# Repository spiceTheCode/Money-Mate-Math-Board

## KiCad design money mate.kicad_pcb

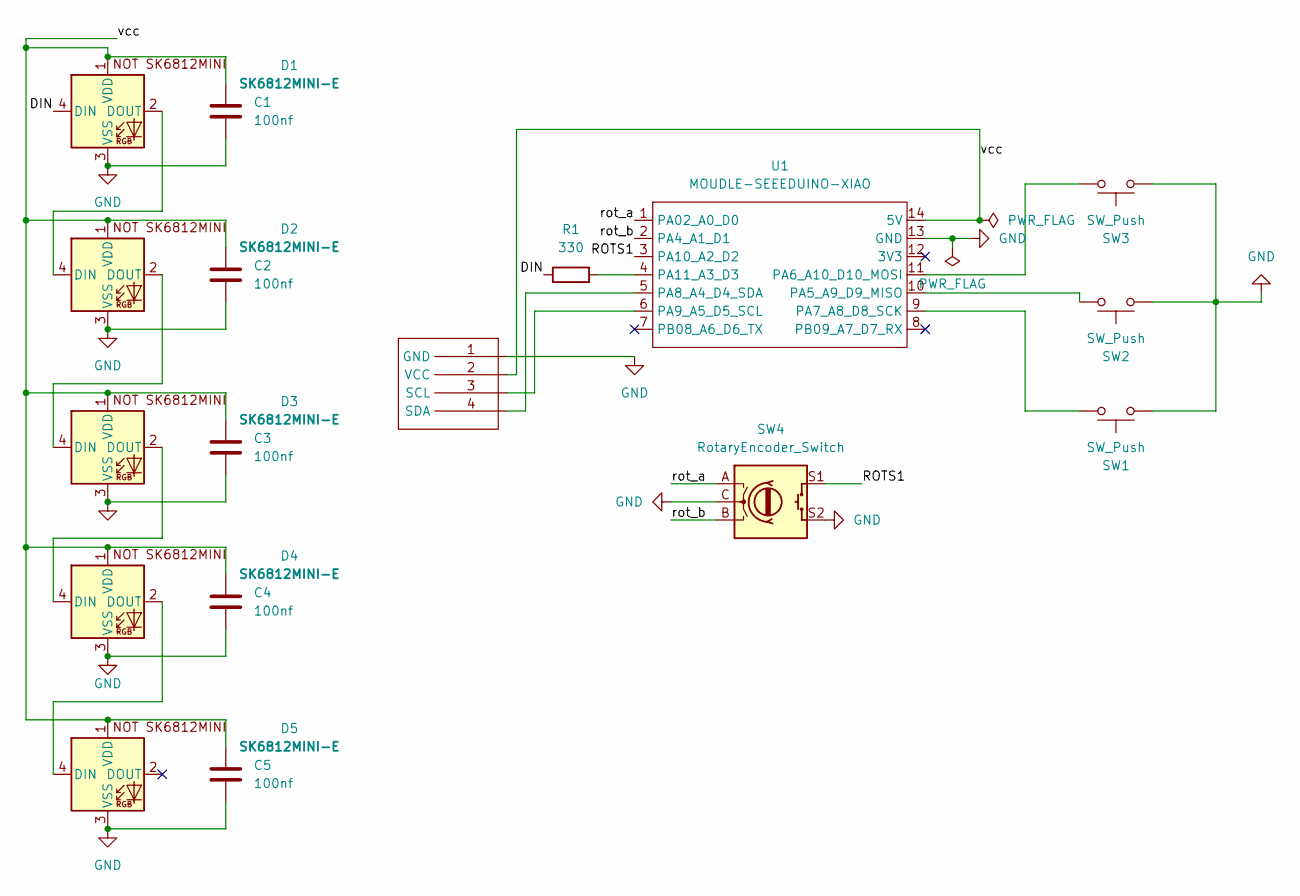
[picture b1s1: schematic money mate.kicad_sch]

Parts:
C1, C2, C3, C4, C5: 100nf; C_0805_2012Metric
D1, D2, D3, D4, D5: SK6812MINI-E; LED_SK6812MINI-E_3.2x2.8mm_P1.5mm_ReverseMount
R1: 330; R_0805_2012Metric
SW1, SW2, SW3: SW_Push; SW_Cherry_MX_1.00u_PCB
SW4: RotaryEncoder_Switch; RotaryEncoder_Alps_EC12E-Switch_Vertical_H20mm
U1: MOUDLE-SEEEDUINO-XIAO; XIAO-Generic-Hybrid-14P-2.54-21X17.8MM
U2: SSD1306-0.91-OLED-4pin-128x32

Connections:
/DIN: D1.4 (DIN), R1.1
/ROTS1: SW4.S1, U1.3 (PA10_A2_D2)
/rot_a: SW4.A, U1.1 (PA02_A0_D0)
/rot_b: SW4.B, U1.2 (PA4_A1_D1)
/vcc: C1.1, C2.1, C3.1, C4.1, C5.1, D1.1 (VDD), D2.1 (VDD), D3.1 (VDD), D4.1 (VDD), D5.1 (VDD), U1.14 (5V), U2.2 (VCC)
GND: C1.2, C2.2, C3.2, C4.2, C5.2, D1.3 (VSS), D2.3 (VSS), D3.3 (VSS), D4.3 (VSS), D5.3 (VSS), SW1.2, SW2.2, SW3.2, SW4.C, SW4.S2, U1.13 (GND), U2.1 (GND)
unnamed: D1.2 (DOUT), D2.4 (DIN)
unnamed: D2.2 (DOUT), D3.4 (DIN)
unnamed: D3.2 (DOUT), D4.4 (DIN)
unnamed: D4.2 (DOUT), D5.4 (DIN)
unnamed: SW2.1, U1.10 (PA5_A9_D9_MISO)
unnamed: SW3.1, U1.11 (PA6_A10_D10_MOSI)
unnamed: SW1.1, U1.9 (PA7_A8_D8_SCK)
unnamed: U1.5 (PA8_A4_D4_SDA), U2.4 (SDA)
unnamed: U1.6 (PA9_A5_D5_SCL), U2.3 (SCL)
unnamed: R1.2, U1.4 (PA11_A3_D3)

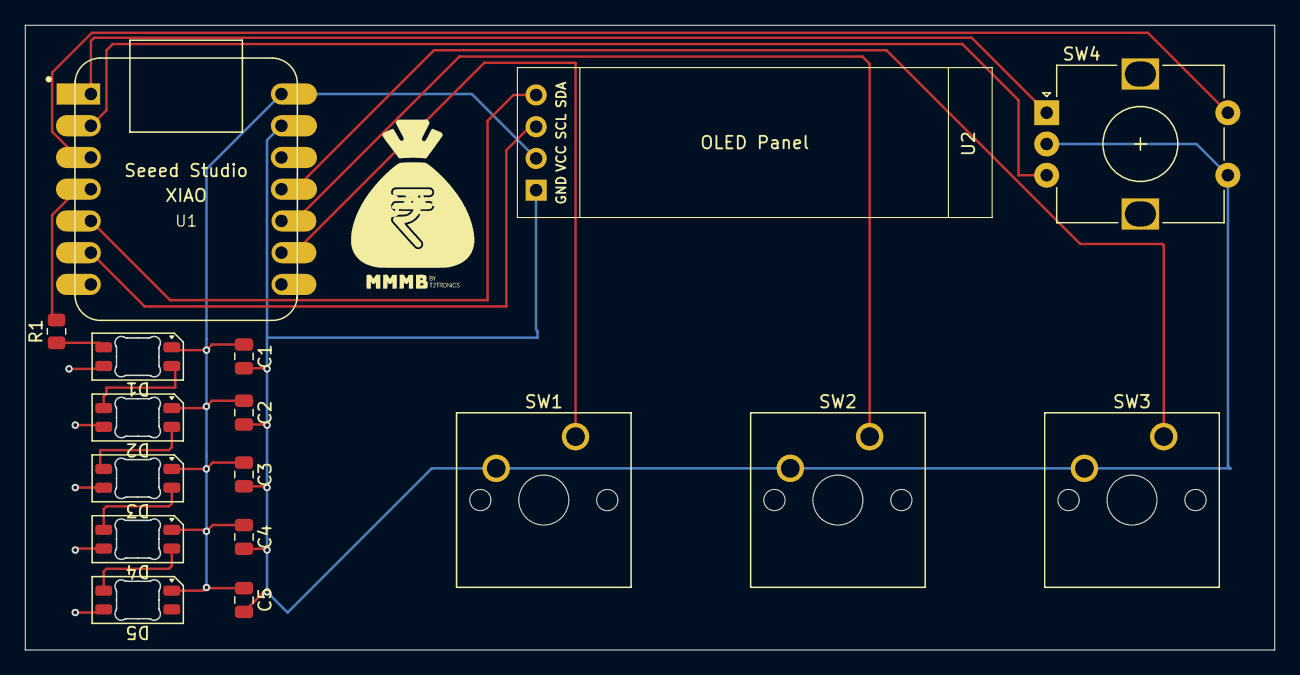
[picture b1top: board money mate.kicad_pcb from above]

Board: 2 copper layers, 100.0 x 50.0 mm, 17 parts (0 on the bottom side), 16 nets.
